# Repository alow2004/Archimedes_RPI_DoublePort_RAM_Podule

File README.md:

# Archimedes_RPI_DoublePort_RAM_Podule

Author: Alain.Lowet

First commit date: 20/09/2023

Subjects: Creation of an Acorn Archimedes podule to communicate with a Raspberry pi via an IDT double port RAM

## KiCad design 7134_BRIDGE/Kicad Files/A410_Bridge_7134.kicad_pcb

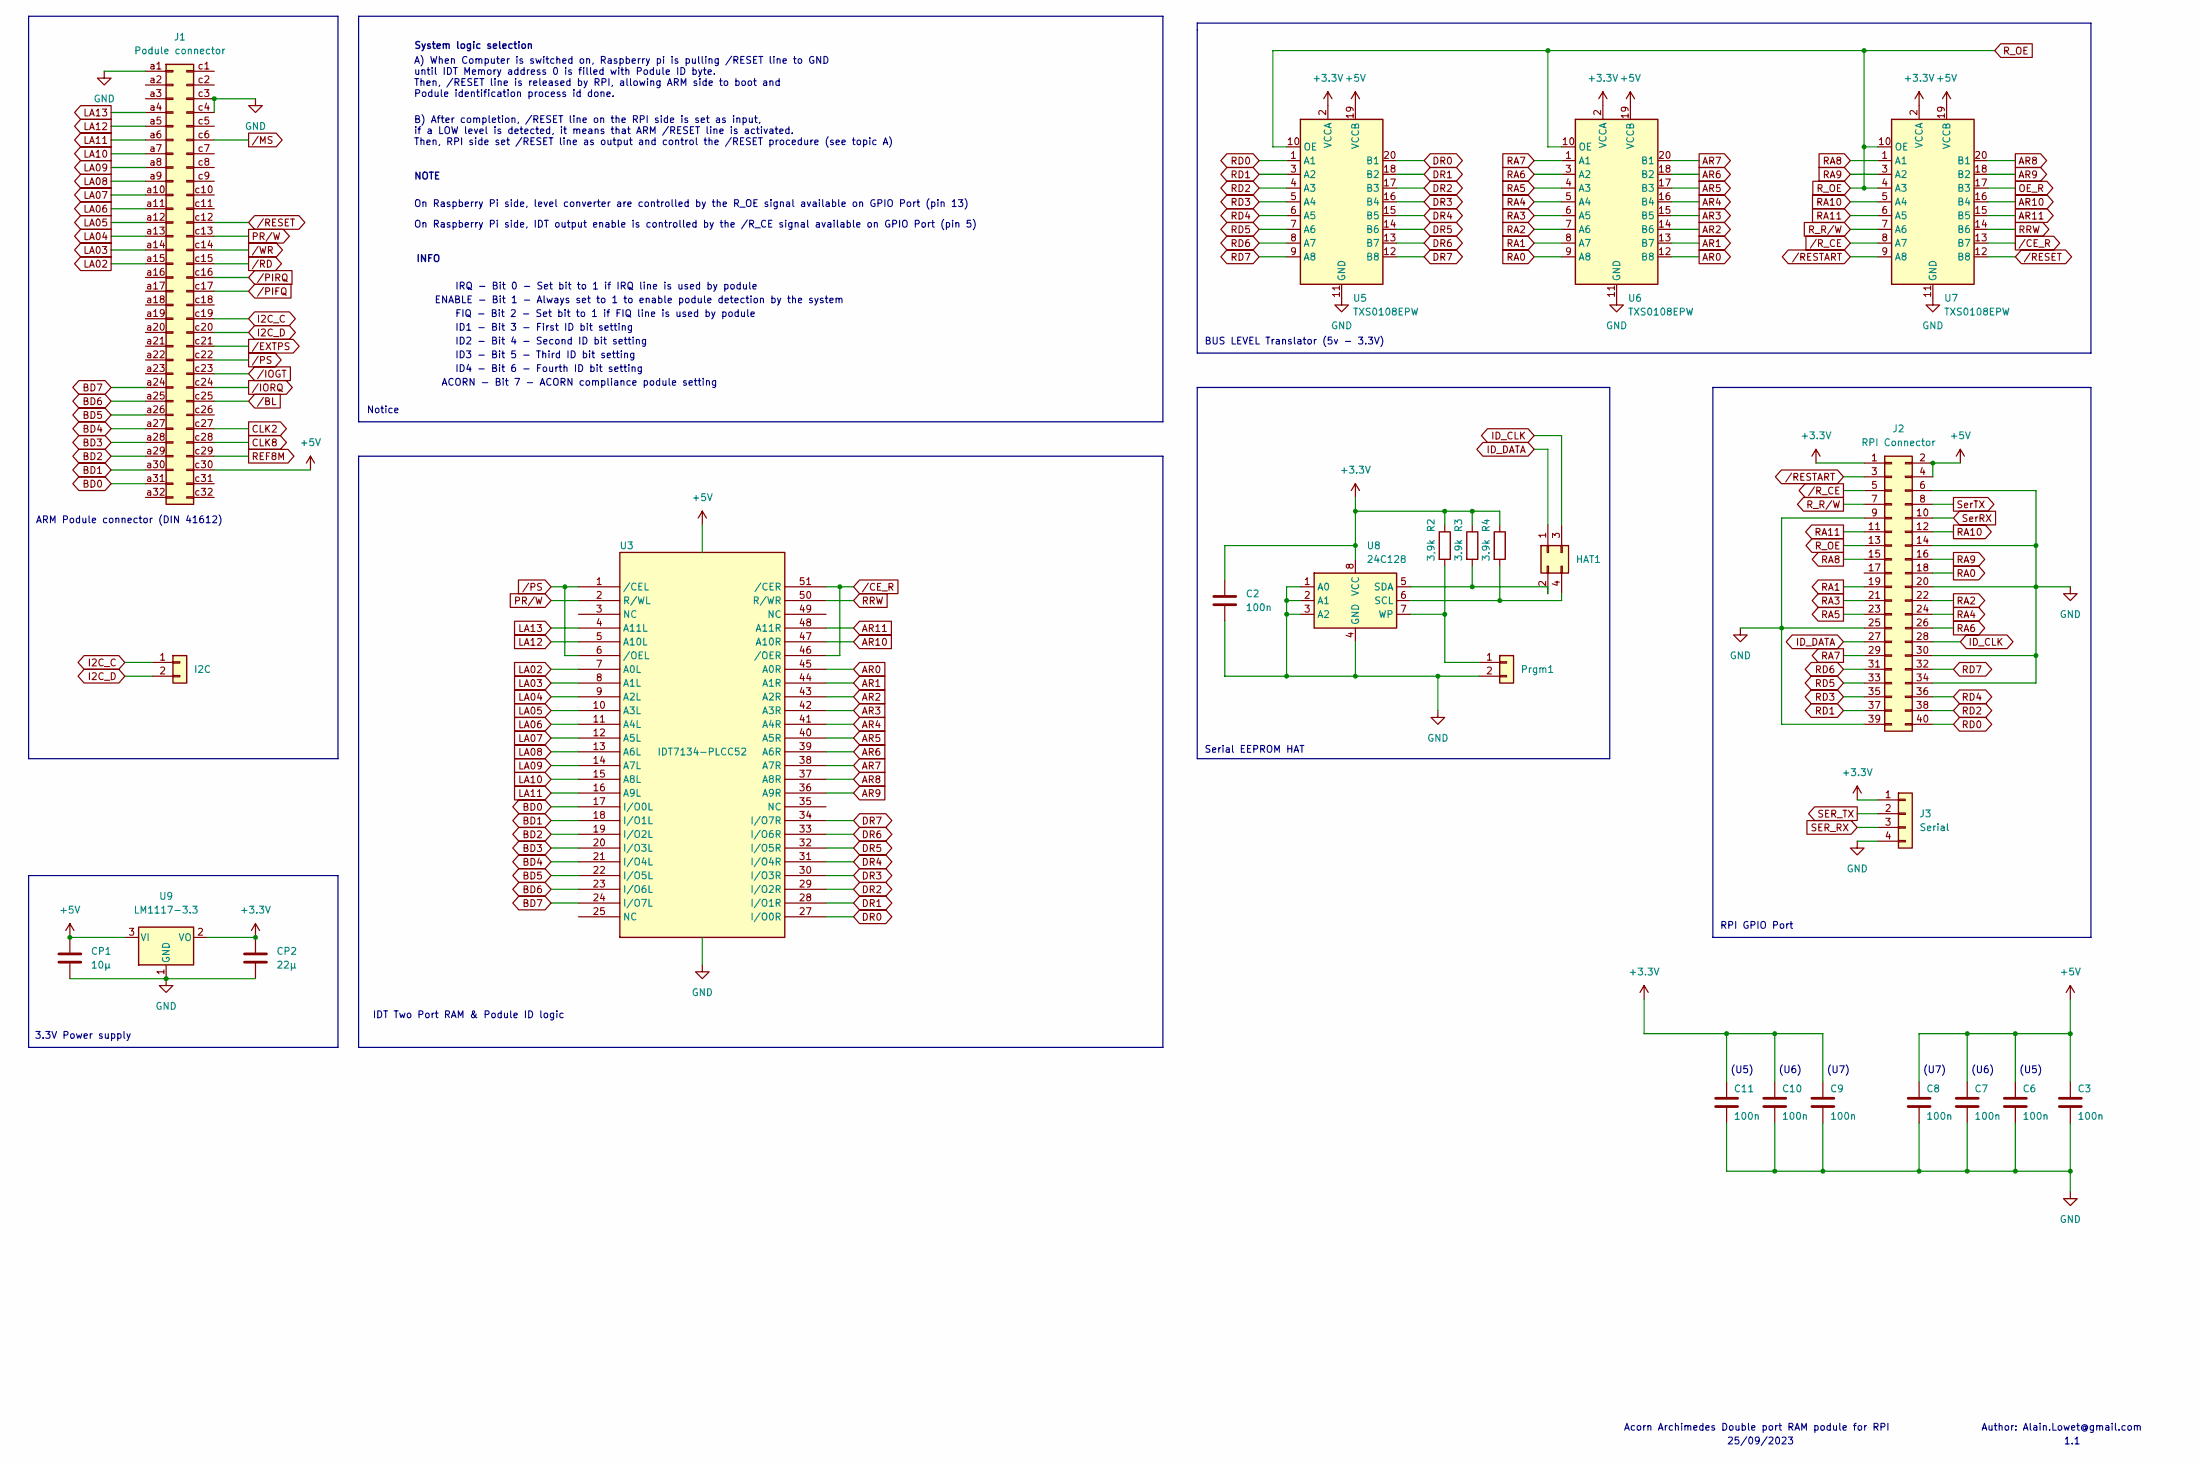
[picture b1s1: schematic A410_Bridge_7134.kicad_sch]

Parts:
C2, C3, C6, C7, C8, C9, C10, C11: 100n; C_1210_3225Metric_Pad1.33x2.70mm_HandSolder
CP1: 10µ; CP_Radial_D8.0mm_P5.00mm
CP2: 22µ; CP_Radial_D8.0mm_P5.00mm
HAT1: Conn_02x02_Odd_Even; PinHeader_2x02_P2.54mm_Vertical
I2C: Prgm; PinHeader_1x02_P2.54mm_Vertical
J1: Podule connector; DIN41612_R_2x32_Male_Horizontal_THT
J2: RPI Connector; PinHeader_2x20_P2.54mm_Vertical
J3: Serial; PinHeader_1x04_P2.54mm_Vertical
Prgm1: Prgm; PinHeader_1x02_P2.54mm_Vertical
R2: 3,9k; R_1210_3225Metric_Pad1.30x2.65mm_HandSolder
R3, R4: 3.9k; R_1210_3225Metric_Pad1.30x2.65mm_HandSolder
U3: IDT7134-PLCC52; PLCC-52_THT-Socket
U5, U6, U7: TXS0108EPW; TSSOP-20_4.4x6.5mm_P0.65mm
U8: 24C128; SOIC-8W_5.3x5.3mm_P1.27mm
U9: LM1117-3.3; SOT-223-3_TabPin2

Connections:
+3.3V: C2.1, C9.1, C10.1, C11.1, CP2.1, J2.1, J3.1, R2.1, R3.1, R4.1, U5.2 (VCCA), U6.2 (VCCA), U7.2 (VCCA), U8.8 (VCC), U9.2 (VO)
+5V: C3.1, C6.1, C7.1, C8.1, CP1.1, J1.c30, J2.2, J2.4, U3.52 (VCC), U5.19 (VCCB), U6.19 (VCCB), U7.19 (VCCB), U9.3 (VI)
AR0: U3.45 (A0R), U6.12 (B8)
AR1: U3.44 (A1R), U6.13 (B7)
AR2: U3.43 (A2R), U6.14 (B6)
AR3: U3.42 (A3R), U6.15 (B5)
AR4: U3.41 (A4R), U6.16 (B4)
AR5: U3.40 (A5R), U6.17 (B3)
AR6: U3.39 (A6R), U6.18 (B2)
AR7: U3.38 (A7R), U6.20 (B1)
AR8: U3.37 (A8R), U7.20 (B1)
AR9: U3.36 (A9R), U7.18 (B2)
AR10: U3.47 (A10R), U7.16 (B4)
AR11: U3.48 (A11R), U7.15 (B5)
BD0: J1.a31, U3.17 (I/O0L)
BD1: J1.a30, U3.18 (I/O1L)
BD2: J1.a29, U3.19 (I/O2L)
BD3: J1.a28, U3.20 (I/O3L)
BD4: J1.a27, U3.21 (I/O4L)
BD5: J1.a26, U3.22 (I/O5L)
BD6: J1.a25, U3.23 (I/O6L)
BD7: J1.a24, U3.24 (I/O7L)
CLK2: J1.c27
CLK8: J1.c28
DR0: U3.27 (I/O0R), U5.20 (B1)
DR1: U3.28 (I/O1R), U5.18 (B2)
DR2: U3.29 (I/O2R), U5.17 (B3)
DR3: U3.30 (I/O3R), U5.16 (B4)
DR4: U3.31 (I/O4R), U5.15 (B5)
DR5: U3.32 (I/O5R), U5.14 (B6)
DR6: U3.33 (I/O6R), U5.13 (B7)
DR7: U3.34 (I/O7R), U5.12 (B8)
GND: C2.2, C3.2, C6.2, C7.2, C8.2, C9.2, C10.2, C11.2, CP1.2, CP2.2, J1.a1, J1.c3, J1.c4, J2.6, J2.9, J2.14, J2.20, J2.25, J2.30, J2.34, J2.39, J3.4, Prgm1.2, U3.26 (GND), U5.11 (GND), U6.11 (GND), U7.11 (GND), U8.1 (A0), U8.2 (A1), U8.3 (A2), U8.4 (GND), U9.1 (GND)
I2C_C: I2C.1, J1.c19
I2C_D: I2C.2, J1.c20
ID_CLK: HAT1.3, J2.28
ID_DATA: HAT1.1, J2.27
LA02: J1.a15, U3.7 (A0L)
LA03: J1.a14, U3.8 (A1L)
LA04: J1.a13, U3.9 (A2L)
LA05: J1.a12, U3.10 (A3L)
LA06: J1.a11, U3.11 (A4L)
LA07: J1.a10, U3.12 (A5L)
LA08: J1.a9, U3.13 (A6L)
LA09: J1.a8, U3.14 (A7L)
LA10: J1.a7, U3.15 (A8L)
LA11: J1.a6, U3.16 (A9L)
LA12: J1.a5, U3.5 (A10L)
LA13: J1.a4, U3.4 (A11L)
unnamed: HAT1.2, R3.2, U8.5 (SDA)
unnamed: HAT1.4, R4.2, U8.6 (SCL)
unnamed: Prgm1.1, R2.2, U8.7 (WP)
OE_R: U7.17 (B3)
PR/W: J1.c13, U3.2 (R/WL)
RA0: J2.18, U6.9 (A8)
RA1: J2.19, U6.8 (A7)
RA2: J2.22, U6.7 (A6)
RA3: J2.21, U6.6 (A5)
RA4: J2.24, U6.5 (A4)
RA5: J2.23, U6.4 (A3)
RA6: J2.26, U6.3 (A2)
RA7: J2.29, U6.1 (A1)
RA8: J2.15, U7.1 (A1)
RA9: J2.16, U7.3 (A2)
RA10: J2.12, U7.5 (A4)
RA11: J2.11, U7.6 (A5)
RD0: J2.40, U5.1 (A1)
RD1: J2.37, U5.3 (A2)
RD2: J2.38, U5.4 (A3)
RD3: J2.35, U5.5 (A4)
RD4: J2.36, U5.6 (A5)
RD5: J2.33, U5.7 (A6)
RD6: J2.31, U5.8 (A7)
RD7: J2.32, U5.9 (A8)
REF8M: J1.c29
RRW: U3.50 (R/WR), U7.14 (B6)
R_OE: J2.13, U5.10 (OE), U6.10 (OE), U7.4 (A3), U7.10 (OE)
R_R/W: J2.7, U7.7 (A6)
SER_RX: J3.3
SER_TX: J3.2
SerRX: J2.10
SerTX: J2.8
/BL: J1.c25
/CE_R: U3.46 (/OER), U3.51 (/CER), U7.13 (B7)
/EXTPS: J1.c21
/IOGT: J1.c23
/IORQ: J1.c24
/MS: J1.c6
/PIFQ: J1.c17
/PIRQ: J1.c16
/PS: J1.c22, U3.1 (/CEL), U3.6 (/OEL)
/RD: J1.c15
/RESET: J1.c12, U7.12 (B8)
/RESTART: J2.3, U7.9 (A8)
/R_CE: J2.5, U7.8 (A7)
/WR: J1.c14

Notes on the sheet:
(U5)
ID4 - Bit 6 - Fourth ID bit setting
RPI GPIO Port
ARM Podule connector (DIN 41612)
System logic selection
On Raspberry Pi side, IDT output enable is controlled by the /R_CE signal available on GPIO Port (pin 5)
ID3 - Bit 5 - Third ID bit setting
ENABLE - Bit 1 - Always set to 1 to enable podule detection by the system
NOTE
(U7)
ID1 - Bit 3 - First ID bit setting
Acorn Archimedes Double port RAM podule for RPI
Notice
INFO
On Raspberry Pi side, level converter are controlled by the R_OE signal available on GPIO Port (pin 13)
3.3V Power supply
Serial EEPROM HAT
1.1
FIQ - Bit 2 - Set bit to 1 if FIQ line is used by podule
B) After completion, /RESET line on the RPI side is set as input, if a LOW level is detected, it means that ARM /RESET line is activated. Then, RPI side set /RESET line as output and control the /RESET procedure (see topic A)
(U6)
ACORN - Bit 7 - ACORN compliance podule setting
BUS LEVEL Translator (5v - 3.3V)
IDT Two Port RAM & Podule ID logic
A) When Computer is switched on, Raspberry pi is pulling /RESET line to GND until IDT Memory address 0 is filled with Podule ID byte. Then, /RESET line is released by RPI, allowing ARM side to boot and Podule identification process id done.
Author: Alain.Lowet@gmail.com
25/09/2023
IRQ - Bit 0 - Set bit to 1 if IRQ line is used by podule
ID2 - Bit 4 - Second ID bit setting

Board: 2 copper layers, 24 parts (0 on the bottom side), 77 nets, no tracks yet.

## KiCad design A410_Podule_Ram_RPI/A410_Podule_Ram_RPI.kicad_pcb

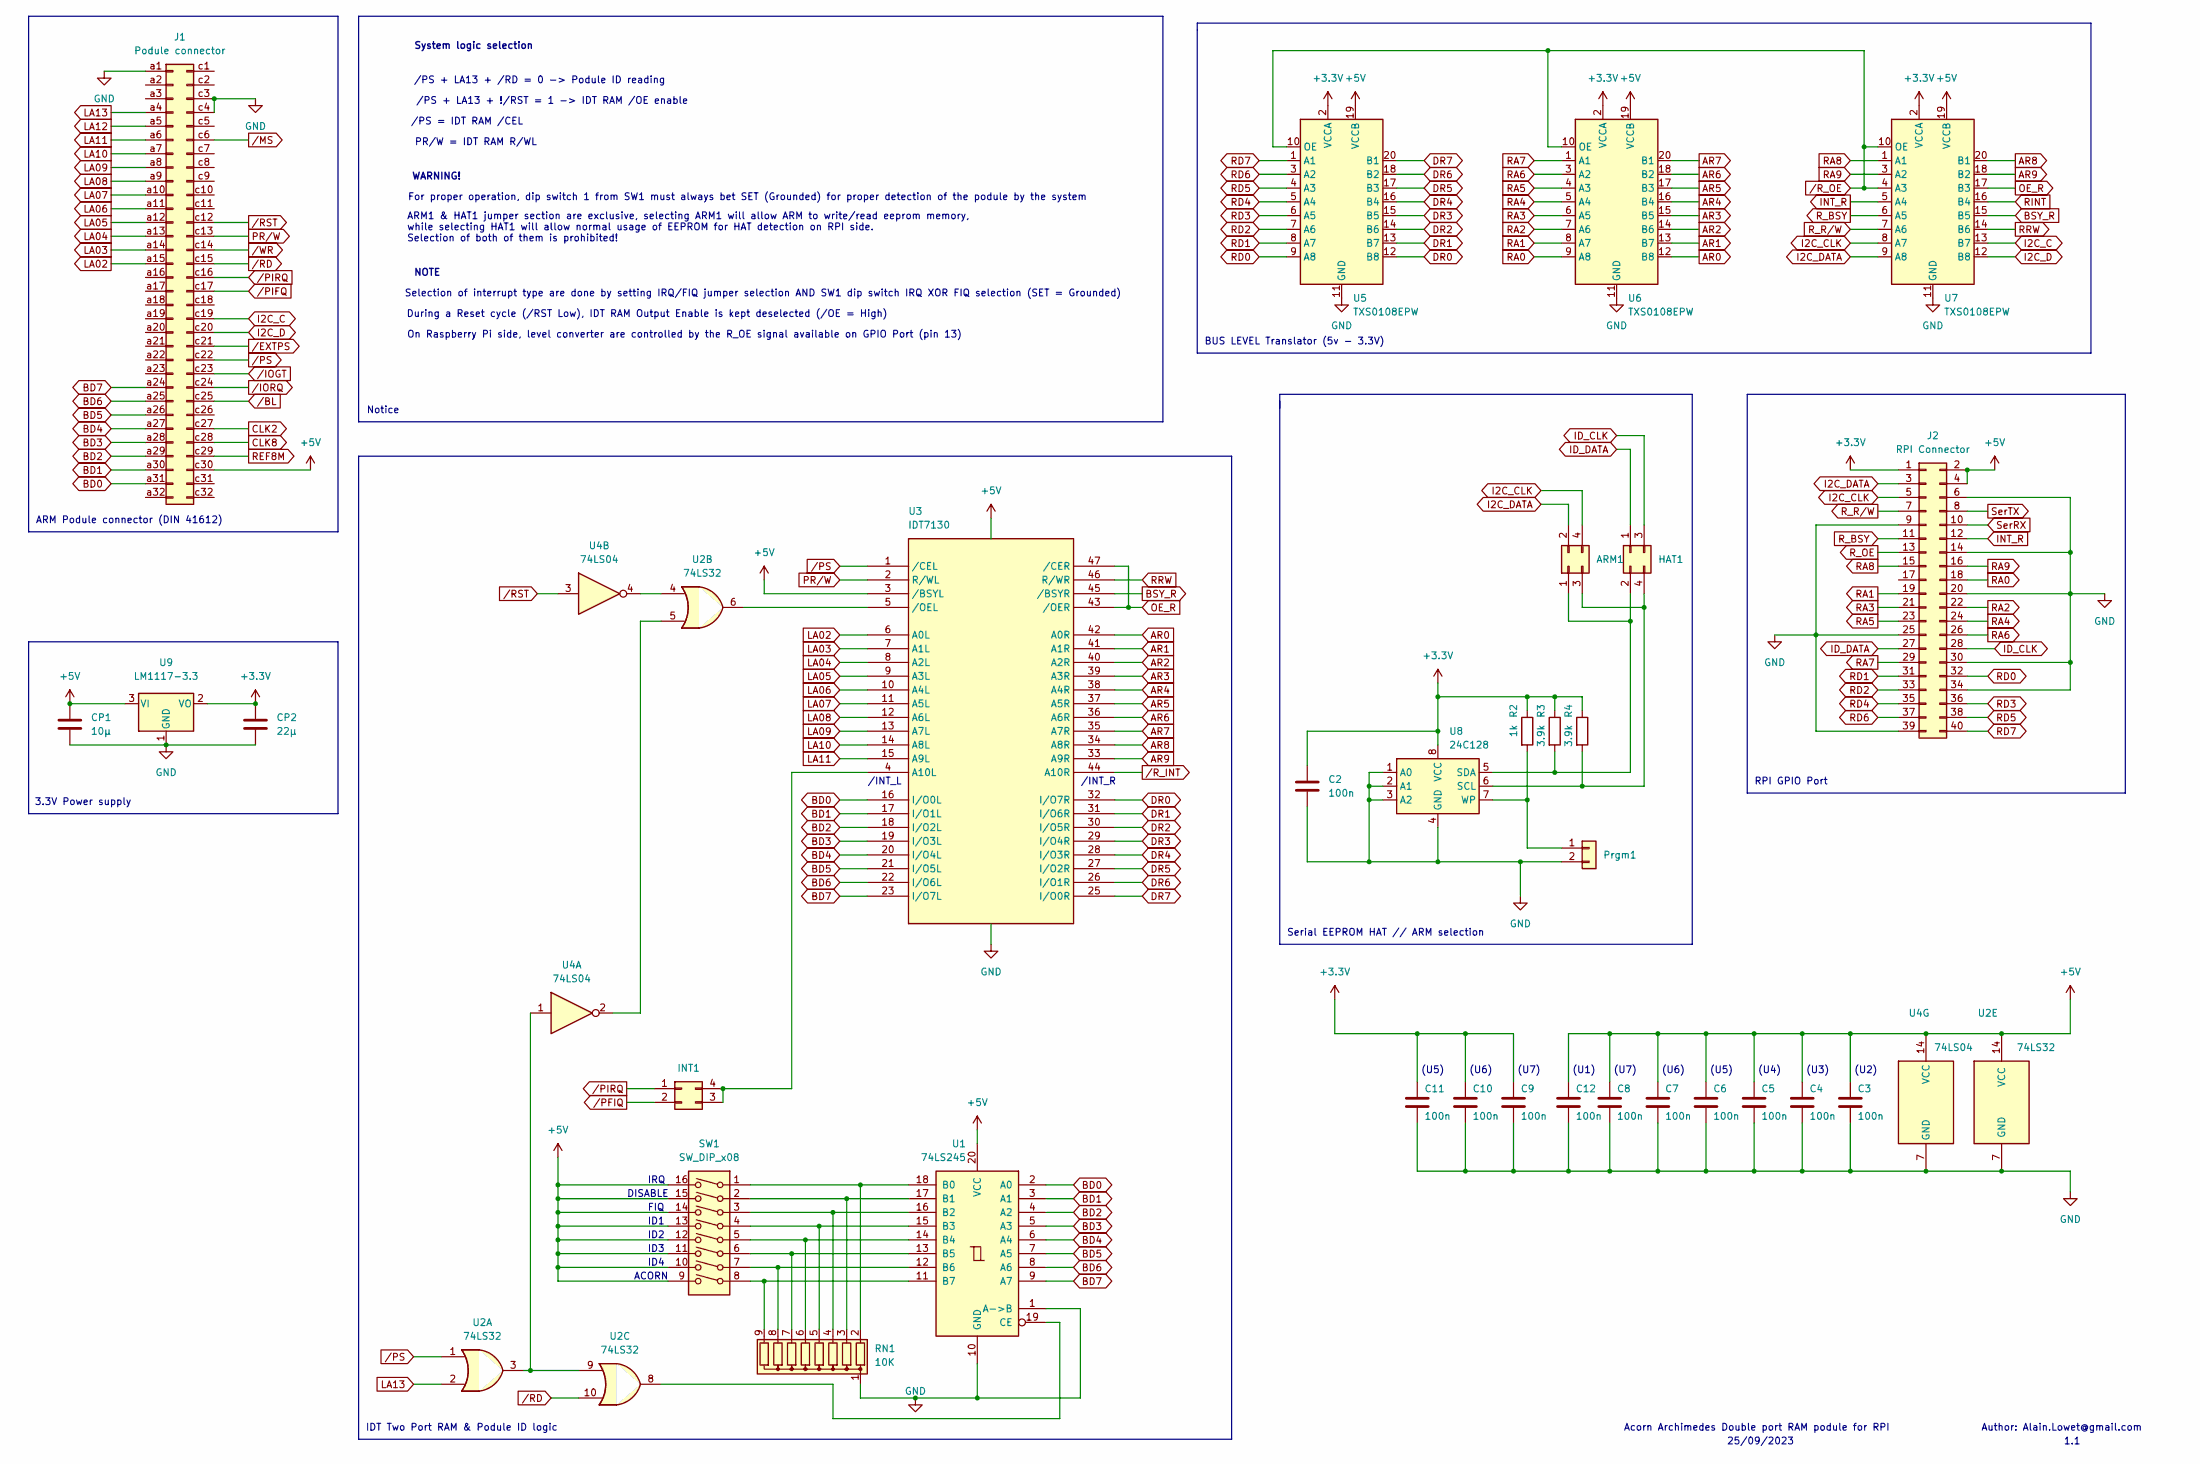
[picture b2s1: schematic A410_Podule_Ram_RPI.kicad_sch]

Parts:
ARM1: Conn_02x02_Odd_Even; PinHeader_2x02_P2.54mm_Vertical
C2, C3, C4, C5, C6, C7, C8, C9, C10, C11, C12: 100n; C_1210_3225Metric_Pad1.33x2.70mm_HandSolder
CP1: 10µ; CP_Radial_D8.0mm_P5.00mm
CP2: 22µ; CP_Radial_D8.0mm_P5.00mm
HAT1: Conn_02x02_Odd_Even; PinHeader_2x02_P2.54mm_Vertical
INT1: INT; PinHeader_2x02_P2.54mm_Vertical
J1: Podule connector; DIN41612_R_2x32_Male_Horizontal_THT
J2: RPI Connector; PinHeader_2x20_P2.54mm_Vertical
Prgm1: Prgm; PinHeader_1x02_P2.54mm_Vertical
R2: 1k; R_1210_3225Metric_Pad1.30x2.65mm_HandSolder
R3, R4: 3.9k; R_1210_3225Metric_Pad1.30x2.65mm_HandSolder
RN1: 10K; R_Array_SIP9
SW1: SW_DIP_x08; DIP-16_W7.62mm_Socket
U1: 74LS245; DIP-20_W7.62mm_Socket
U2: 74LS32; DIP-14_W7.62mm_Socket
U3: IDT7130; DIP-48_W15.24mm_Socket
U4: 74LS04; DIP-14_W7.62mm_Socket
U5, U6, U7: TXS0108EPW; TSSOP-20_4.4x6.5mm_P0.65mm
U8: 24C128; SOIC-8W_5.3x5.3mm_P1.27mm
U9: LM1117-3.3; SOT-223-3_TabPin2

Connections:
+3.3V: C2.1, C9.1, C10.1, C11.1, CP2.1, J2.1, R2.1, R3.1, R4.1, U5.2 (VCCA), U6.2 (VCCA), U7.2 (VCCA), U8.8 (VCC), U9.2 (VO)
+5V: C3.1, C4.1, C5.1, C6.1, C7.1, C8.1, C12.1, CP1.1, J1.c30, J2.2, J2.4, SW1.9, SW1.10, SW1.11, SW1.12, SW1.13, SW1.14, SW1.15, SW1.16, U1.20 (VCC), U2.14 (VCC), U3.48 (VCC), U4.14 (VCC), U5.19 (VCCB), U6.19 (VCCB), U7.19 (VCCB), U9.3 (VI)
AR0: U3.42 (A0R), U6.12 (B8)
AR1: U3.41 (A1R), U6.13 (B7)
AR2: U3.40 (A2R), U6.14 (B6)
AR3: U3.39 (A3R), U6.15 (B5)
AR4: U3.38 (A4R), U6.16 (B4)
AR5: U3.37 (A5R), U6.17 (B3)
AR6: U3.36 (A6R), U6.18 (B2)
AR7: U3.35 (A7R), U6.20 (B1)
AR8: U3.34 (A8R), U7.20 (B1)
AR9: U3.33 (A9R), U7.18 (B2)
BD0: J1.a31, U1.2 (A0), U3.16 (I/O0L)
BD1: J1.a30, U1.3 (A1), U3.17 (I/O1L)
BD2: J1.a29, U1.4 (A2), U3.18 (I/O2L)
BD3: J1.a28, U1.5 (A3), U3.19 (I/O3L)
BD4: J1.a27, U1.6 (A4), U3.20 (I/O4L)
BD5: J1.a26, U1.7 (A5), U3.21 (I/O5L)
BD6: J1.a25, U1.8 (A6), U3.22 (I/O6L)
BD7: J1.a24, U1.9 (A7), U3.23 (I/O7L)
BSY_R: U3.45 (/BSYR), U7.15 (B5)
CLK2: J1.c27
CLK8: J1.c28
DR0: U3.32 (I/O7R), U5.12 (B8)
DR1: U3.31 (I/O6R), U5.13 (B7)
DR2: U3.30 (I/O5R), U5.14 (B6)
DR3: U3.29 (I/O4R), U5.15 (B5)
DR4: U3.28 (I/O3R), U5.16 (B4)
DR5: U3.27 (I/O2R), U5.17 (B3)
DR6: U3.26 (I/O1R), U5.18 (B2)
DR7: U3.25 (I/O0R), U5.20 (B1)
GND: C2.2, C3.2, C4.2, C5.2, C6.2, C7.2, C8.2, C9.2, C10.2, C11.2, C12.2, CP1.2, CP2.2, J1.a1, J1.c3, J1.c4, J2.6, J2.9, J2.14, J2.20, J2.25, J2.30, J2.34, J2.39, Prgm1.2, RN1.1 (common), U1.1 (A->B), U1.10 (GND), U2.7 (GND), U3.24 (GND), U4.7 (GND), U5.11 (GND), U6.11 (GND), U7.11 (GND), U8.1 (A0), U8.2 (A1), U8.3 (A2), U8.4 (GND), U9.1 (GND)
I2C_C: J1.c19, U7.13 (B7)
I2C_CLK: ARM1.4, J2.5, U7.8 (A7)
I2C_D: J1.c20, U7.12 (B8)
I2C_DATA: ARM1.2, J2.3, U7.9 (A8)
ID_CLK: HAT1.3, J2.28
ID_DATA: HAT1.1, J2.27
INT_R: J2.12, U7.5 (A4)
LA02: J1.a15, U3.6 (A0L)
LA03: J1.a14, U3.7 (A1L)
LA04: J1.a13, U3.8 (A2L)
LA05: J1.a12, U3.9 (A3L)
LA06: J1.a11, U3.10 (A4L)
LA07: J1.a10, U3.11 (A5L)
LA08: J1.a9, U3.12 (A6L)
LA09: J1.a8, U3.13 (A7L)
LA10: J1.a7, U3.14 (A8L)
LA11: J1.a6, U3.15 (A9L)
LA12: J1.a5
LA13: J1.a4, U2.2
unnamed: ARM1.1, HAT1.2, R3.2, U8.5 (SDA)
unnamed: ARM1.3, HAT1.4, R4.2, U8.6 (SCL)
unnamed: INT1.3, INT1.4, U3.4 (A10L)
unnamed: Prgm1.1, R2.2, U8.7 (WP)
unnamed: RN1.2 (R1), SW1.1, U1.18 (B0)
unnamed: RN1.3 (R2), SW1.2, U1.17 (B1)
unnamed: RN1.4 (R3), SW1.3, U1.16 (B2)
unnamed: RN1.5 (R4), SW1.4, U1.15 (B3)
unnamed: RN1.6 (R5), SW1.5, U1.14 (B4)
unnamed: RN1.7 (R6), SW1.6, U1.13 (B5)
unnamed: RN1.8 (R7), SW1.7, U1.12 (B6)
unnamed: RN1.9 (R8), SW1.8, U1.11 (B7)
unnamed: U1.19 (CE), U2.8
unnamed: U2.3, U2.9, U4.1
unnamed: U2.4, U4.4
unnamed: U2.5, U4.2
unnamed: U2.6, U3.5 (/OEL)
OE_R: U3.43 (/OER), U3.47 (/CER), U7.17 (B3)
PR/W: J1.c13, U3.2 (R/WL)
RA0: J2.18, U6.9 (A8)
RA1: J2.19, U6.8 (A7)
RA2: J2.22, U6.7 (A6)
RA3: J2.21, U6.6 (A5)
RA4: J2.24, U6.5 (A4)
RA5: J2.23, U6.4 (A3)
RA6: J2.26, U6.3 (A2)
RA7: J2.29, U6.1 (A1)
RA8: J2.15, U7.1 (A1)
RA9: J2.16, U7.3 (A2)
RD0: J2.32, U5.9 (A8)
RD1: J2.31, U5.8 (A7)
RD2: J2.33, U5.7 (A6)
RD3: J2.36, U5.6 (A5)
RD4: J2.35, U5.5 (A4)
RD5: J2.38, U5.4 (A3)
RD6: J2.37, U5.3 (A2)
RD7: J2.40, U5.1 (A1)
REF8M: J1.c29
RINT: U7.16 (B4)
RRW: U3.46 (R/WR), U7.14 (B6)
R_BSY: J2.11, U7.6 (A5)
R_OE: J2.13
R_R/W: J2.7, U7.7 (A6)
SerRX: J2.10
SerTX: J2.8
/BL: J1.c25
/EXTPS: J1.c21
/IOGT: J1.c23
/IORQ: J1.c24
/MS: J1.c6
/PFIQ: INT1.2
/PIFQ: J1.c17
/PIRQ: INT1.1, J1.c16
/PS: J1.c22, U2.1, U3.1 (/CEL)
/RD: J1.c15, U2.10
/RST: J1.c12, U4.3
/R_INT: U3.44 (A10R)
/R_OE: U5.10 (OE), U6.10 (OE), U7.4 (A3), U7.10 (OE)
/WR: J1.c14

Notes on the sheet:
(U5)
RPI GPIO Port
For proper operation, dip switch 1 from SW1 must always bet SET (Grounded) for proper detection of the podule by the system
(U4)
ARM Podule connector (DIN 41612)
System logic selection
ID3
NOTE
(U2)
(U7)
ARM1 & HAT1 jumper section are exclusive, selecting ARM1 will allow ARM to write/read eeprom memory, while selecting HAT1 will allow normal usage of EEPROM for HAT detection on RPI side. Selection of both of them is prohibited!
ID2
(U3)
Acorn Archimedes Double port RAM podule for RPI
Notice
WARNING!
On Raspberry Pi side, level converter are controlled by the R_OE signal available on GPIO Port (pin 13)
(U1)
3.3V Power supply
Serial EEPROM HAT // ARM selection
1.1
Selection of interrupt type are done by setting IRQ/FIQ jumper selection AND SW1 dip switch IRQ XOR FIQ selection (SET = Grounded)
FIQ
/INT_R
ID4
/PS + LA13 + !/RST = 1 -> IDT RAM /OE enable
(U6)
BUS LEVEL Translator (5v - 3.3V)
/INT_L
IDT Two Port RAM & Podule ID logic
/PS + LA13 + /RD = 0 -> Podule ID reading
Author: Alain.Lowet@gmail.com
ID1
25/09/2023
IRQ
DISABLE
PR/W = IDT RAM R/WL
ACORN
/PS = IDT RAM /CEL
During a Reset cycle (/RST Low), IDT RAM Output Enable is kept deselected (/OE = High)

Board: 2 copper layers, 33 parts (0 on the bottom side), 93 nets, no tracks yet.

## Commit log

2023-09-29 Add files via upload
    PCB pictures top&bottom
2023-09-29 Add files via upload
    First draft description on usage of memory allocation, work in progress, subject to a lot of changes!
2023-09-30 Add files via upload
    Added Kicad files...
2023-10-10 Add files via upload
    Some pictures of the received prototype boards
2023-10-23 New IDT 7134 4K * 8 bits double port ram version
    Extend the memory available at maximum permitted podule space
2023-10-25 some picture of rev 1.0 board
2023-10-30 IDT 7134 version, board pictures
2023-10-31 pictures of mounted cards
2023-10-31 Test software

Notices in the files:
7134_BRIDGE/Kicad Files/A410_Bridge_7134.kicad_pcb:
© 2023 - Elitech - ALO
